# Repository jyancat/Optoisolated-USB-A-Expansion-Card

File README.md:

# Optoisolated-USB-A-Expansion-Card
OptoIsolated USB-A Expansion Card using the ADUM4160 for isolation and the ADUM5000ARWZ as a isolated power supply.

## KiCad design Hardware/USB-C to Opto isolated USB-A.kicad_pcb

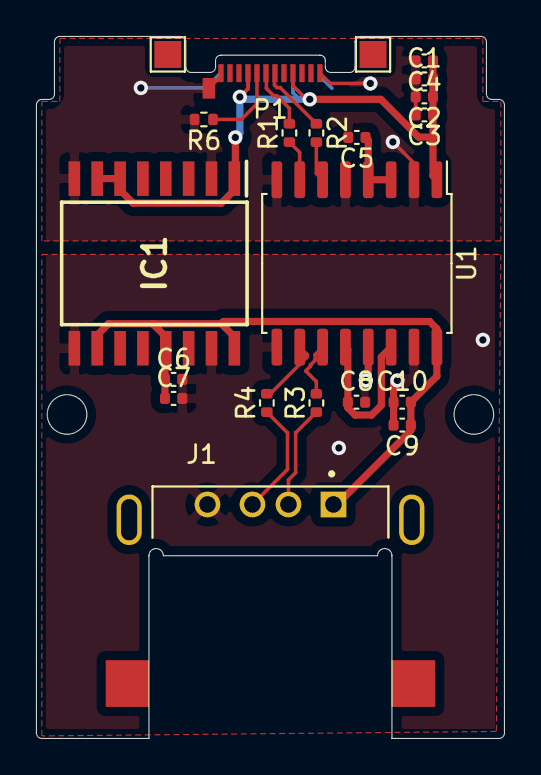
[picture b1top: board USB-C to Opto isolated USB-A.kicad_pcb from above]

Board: 2 copper layers, 26.0 x 39.0 mm, 23 parts (0 on the bottom side), 13 nets.

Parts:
C1, C9: 10uF; C_0402_1005Metric
C2, C3, C4, C5, C6, C7, C8, C10: 0.1uF; C_0402_1005Metric
H1, H2: MountingHole; MountingHole_2.2mm_M2
IC1: ADUM5000ARWZ; SOIC127P1032X265-16N
J1: USB_A; MOLEX_48258-0001
P1: USB_C_Plug_USB2.0; USB_C_Plug_Molex_105444
R1, R2, R3, R4: 24R; R_0402_1005Metric
R6: 5.1K; R_0402_1005Metric
TP1, TP3: TestPoint; TestPoint_Pad_1.5x1.5mm
U1: ADUM4160; SOIC-16W_7.5x10.3mm_P1.27mm

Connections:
/DDN: R3.2, U1.11
/DDP: R4.2, U1.10
D+: P1.A6, R1.1, R1.2, U1.7
D-: P1.A7, R2.1, R2.2, U1.6
DD+: J1.3, R4.1
DD-: J1.2, R3.1
GND: C1.1, C2.2, C3.2, C4.2, C5.2, IC1.2, IC1.8, P1.A1, P1.A12, P1.B1, P1.B12, P1.S1, R6.2, U1.2, U1.5, U1.8
GNDD: C6.2, C7.2, C8.2, C9.2, C10.1, IC1.9, IC1.15, J1.4, U1.9, U1.13, U1.15
unnamed: C5.1, U1.3, U1.4
unnamed: C8.1, U1.12, U1.14
unnamed: P1.A5, R6.1
VCC: C1.2, C2.1, C3.1, C4.1, IC1.1, IC1.6, IC1.7, P1.A4, P1.A9, P1.B4, P1.B9, U1.1
VCCQ: C6.1, C7.1, C9.1, C10.2, IC1.10, IC1.13, IC1.16, J1.1, U1.16

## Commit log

2022-05-28 Updated files
